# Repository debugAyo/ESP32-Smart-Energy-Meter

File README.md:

# ESP32 Smart Energy Meter & Load Controller

So, I got tired of manually toggling between grid power, generators, and inverters while completely guessing how much power everything was drawing. This project is my fix: a custom ESP32-powered smart energy meter that tracks live electrical data and handles automated safety cutoffs without blowing up.

## What This Board Does
- **Keeps things safe:** Uses an HLK-PM01 5V power supply backed up by a 1A fuse and a Metal Oxide Varistor (MOV) so voltage spikes don't fry the board.
- **Tracks the numbers:** Hooks up a PZEM-004T module with a CT clamp to measure real voltage, current, and power usage on the fly.
- **Switches heavy loads:** Uses an optoisolated 5V relay module to trigger a high-voltage AC contactor safely from low-voltage digital pins.
- **Maintains boundaries:** Designed the double-sided KiCad layout with a strict physical isolation gap keeping the spicy 220V AC mains completely away from the low-voltage DC logic.

## Stack & Hardware
- **Brain:** ESP32 DevKit V1 (plugs into carrier headers `J4`/`J5`)
- **CAD & Layout:** KiCad
- **Core Parts:** HLK-PM01, PZEM-004T, 5V relay module, Phoenix screw terminals

## Bill of Materials (BOM) & Budget

| Component | Description | LCSC Part # | Qty | Unit Price | Total Amount |
| :--- | :--- | :--- | :--- | :--- | :--- |
| **ESP32-C3 Module** | ESP32-C3-MINI-1-N4 | [C2838502](https://www.lcsc.com/product-detail/C2838502.html) | 1 | $3.0700 | $3.07 |
| **3.3V LDO Regulator** | AMS1117-3.3 (SOT-223) | [C347222](https://www.lcsc.com/product-detail/C347222.html) | 10 | $0.0491 | $0.49 |
| **USB Type-C Receptacle** | 16-Pin SMD | [C165948](https://www.lcsc.com/product-detail/C165948.html) | 5 | $0.1736 | $0.87 |
| **Tactile Push Buttons** | 3x4mm SMD | [C318884](https://www.lcsc.com/product-detail/C318884.html) | 20 | $0.0208 | $0.42 |
| **Green LED (Through-Hole)** | 3mm THT (D=3mm) | [C85161](https://www.lcsc.com/product-detail/C85161.html) | 20 | $0.0365 | $0.73 |
| **Green LED (Discrete SMD)** | 0805 SMD | [C84260](https://www.lcsc.com/product-detail/C84260.html) | 30 | $0.0223 | $0.67 |
| **Axial Resistors** | 1kΩ 1/4W Carbon Film THT | [C66649](https://www.lcsc.com/product-detail/C66649.html) | 50 | $0.0133 | $0.67 |

### Funding Request Breakdown
* **Merchandise Subtotal:** $7.02
* **LCSC Handling Fee:** $3.00
* **Merchandise Discount:** -$0.10
* **DHL Express Shipping (Nigeria):** $55.65
* **Grand Total:** $65.57

## How to Flash Firmware
To upload code to the onboard ESP32 via the Arduino IDE:
1. Connect the ESP32 board to your computer using a USB cable.
2. Select **ESP32 Dev Module** under **Tools > Board**, and choose the active COM port.
3. If the upload does not start automatically, press and hold the **BOOT** button.
4. When `Connecting.......` appears in the terminal, release the **BOOT** button.
5. Once the upload hits 100%, press the **EN / RST** button once to start the firmware.

## Visuals & Design

### Schematic Capture

### PCB Layout

### 3D Board Render

## Repo Structure
- `Smart_Meter_PoC.kicad_sch` — KiCad schematic file.
- `Smart_Meter_PoC.kicad_pcb` — KiCad PCB layout file.
- `production/` — Generated Gerbers (`SEM-V1_gerbers.zip`), BOM, and position files.
- `images/` — Visual assets and screenshots.
- `firmware/` — Microcontroller test and operational firmware.
- `JOURNAL.md` — Build log, time tracking, and workflow notes.

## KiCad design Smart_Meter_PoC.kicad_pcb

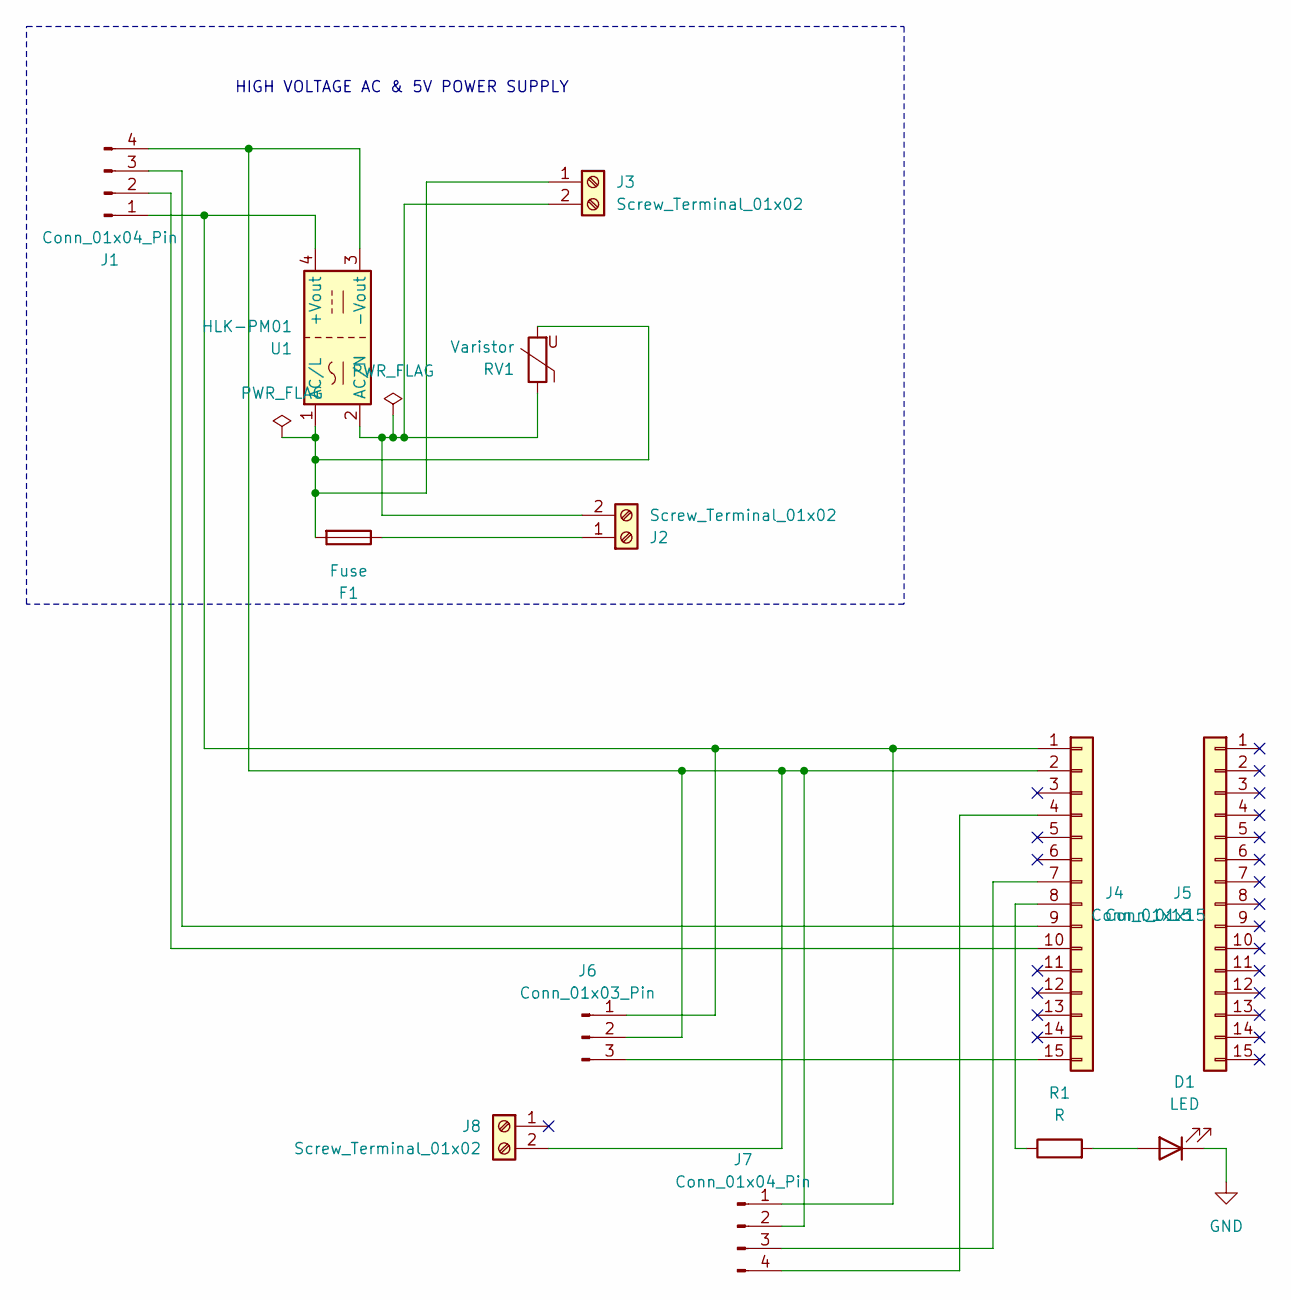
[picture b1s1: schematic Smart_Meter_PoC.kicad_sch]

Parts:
D1: LED; LED_D5.0mm
F1: Fuse; Fuseholder_Cylinder-5x20mm_Schurter_FPG4_Vertical_Closed
J1, J7: Conn_01x04_Pin; PinHeader_1x04_P2.54mm_Vertical
J2, J3, J8: Screw_Terminal_01x02; TerminalBlock_Phoenix_MKDS-1,5-2_1x02_P5.00mm_Horizontal
J4, J5: Conn_01x15; PinHeader_1x15_P2.54mm_Vertical
J6: Conn_01x03_Pin; PinHeader_1x03_P2.54mm_Vertical
R1: R; R_Axial_DIN0207_L6.3mm_D2.5mm_P10.16mm_Horizontal
RV1: Varistor; RV_Disc_D7mm_W3.4mm_P5mm
U1: HLK-PM01; Converter_ACDC_Hi-Link_HLK-PMxx

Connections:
GND: D1.1 (K)
unnamed: D1.2 (A), R1.2
unnamed: J1.1, J4.1, J6.1, J7.1, U1.4 (+Vout)
unnamed: J1.2, J4.10
unnamed: J1.3, J4.9
unnamed: J1.4, J4.2, J6.2, J7.2, J8.2 (Pin_2_2), U1.3 (-Vout)
unnamed: F1.1, J2.1
unnamed: J2.2, J3.2, RV1.1, U1.2 (AC/N)
unnamed: F1.2, J3.1, RV1.2, U1.1 (AC/L)
unnamed: J4.4, J7.4
unnamed: J4.7, J7.3
unnamed: J4.8, R1.1
unnamed: J4.15, J6.3

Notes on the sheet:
HIGH VOLTAGE AC & 5V POWER SUPPLY

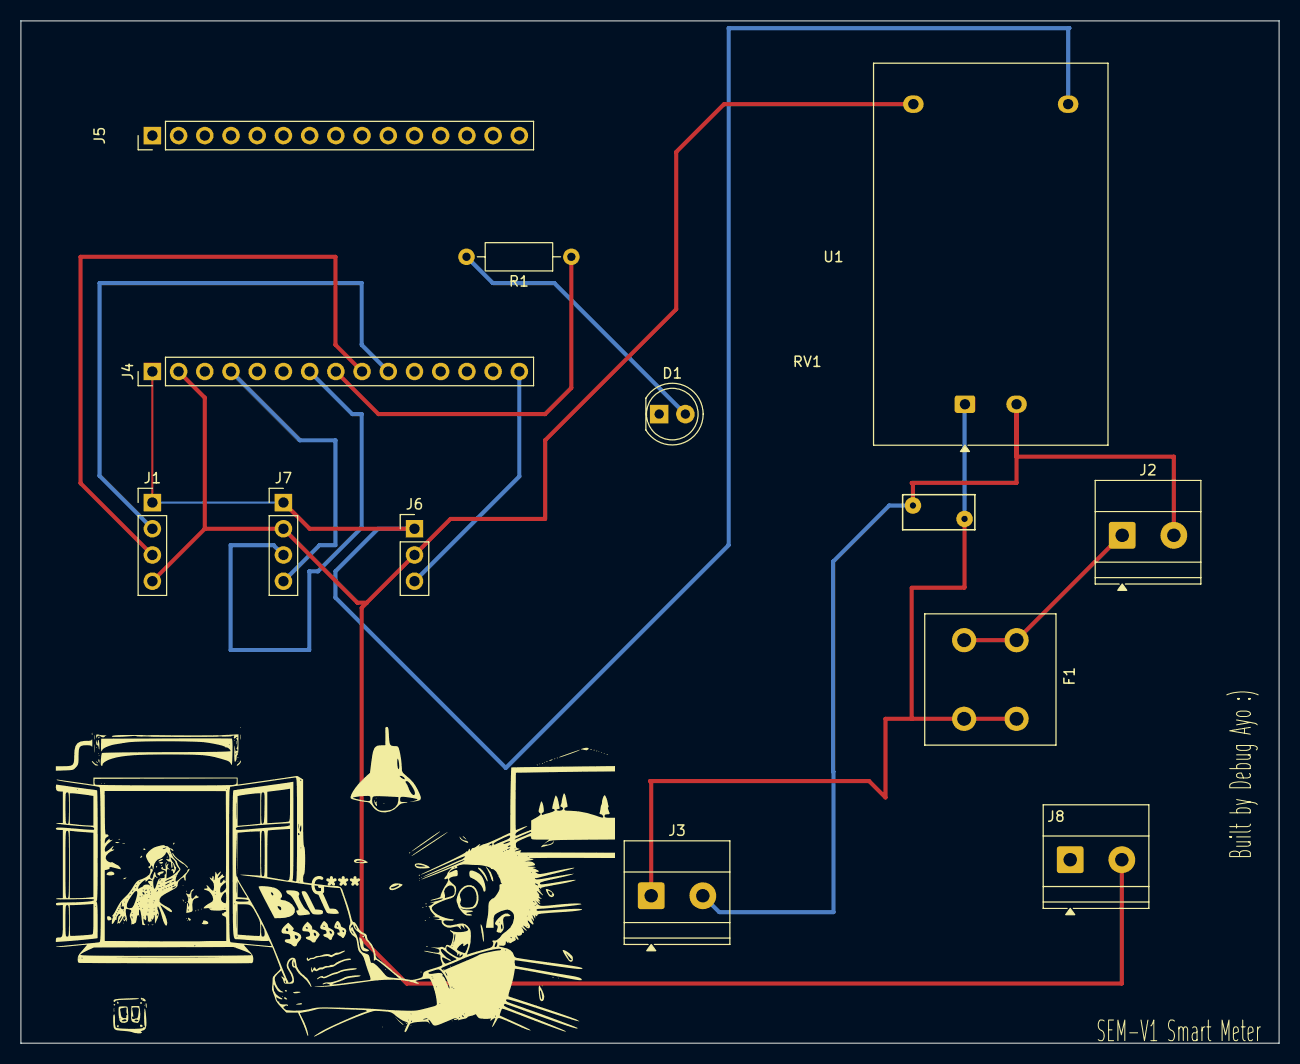
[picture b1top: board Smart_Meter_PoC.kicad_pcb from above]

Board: 2 copper layers, 121.9 x 99.1 mm, 13 parts (0 on the bottom side), 12 nets.
